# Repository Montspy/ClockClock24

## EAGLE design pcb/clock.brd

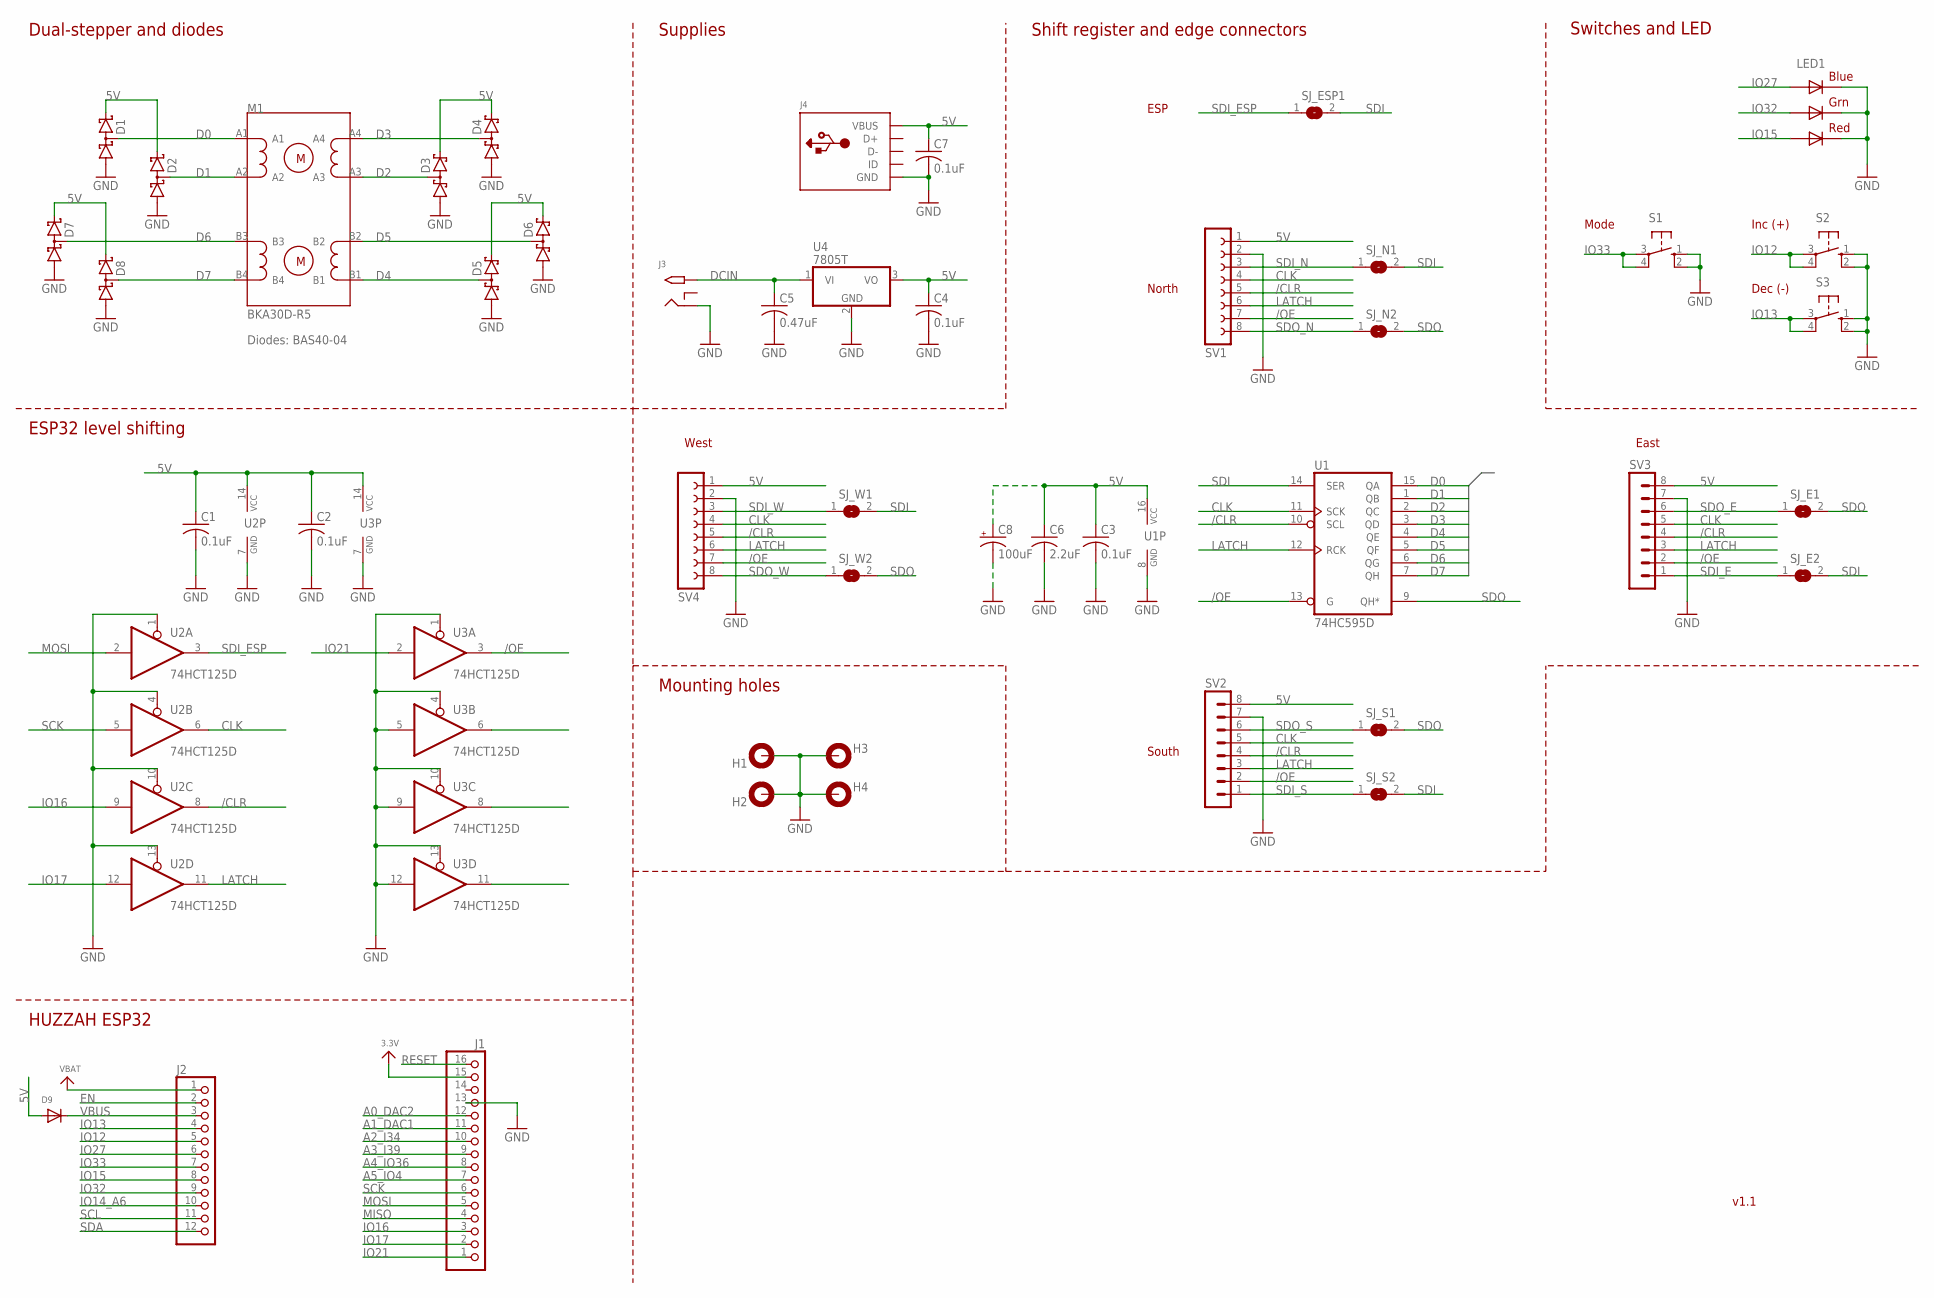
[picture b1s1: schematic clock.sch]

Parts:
C1, C2, C3, C4, C7: 0.1uF; C0805K
C5: 0.47uF; C0805K
C6: 2.2uF; C0805K
C8: 100uF; E3,5-8
D1, D2, D3, D4, D5, D6, D7, D8: BAS40-04; SOT23
D9: DIODEDO-1N4148; DO-1N4148
H1, H2, H3, H4: MOUNT-PAD-ROUND3.2; 3,2-PAD
J1: HEADER-1X16_MIN; 1X16_ROUND_MIN
J2: HEADER-1X12_MIN; 1X12_ROUND_MIN
J3: 2.1MMJACKTHM; PJ-102A
J4: USBMINIB; USB-MINIB
LED1: RGBLED5050
M1: BKA30D-R5
S1, S2, S3: 10-XX; B3F-10XX
SJ_E1, SJ_E2: SJ
SJ_ESP1: SJ
SJ_N1, SJ_N2: SJ
SJ_S1, SJ_S2: SJ
SJ_W1, SJ_W2: SJ
SV1, SV4: FE08W
SV2, SV3: MA08-1W
U1: 74HC595D; SO16
U2, U3: 74HCT125D; SO14
U4: 7805T; TO220H

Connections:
3.3V: J1.15
5V: C1.1, C2.1, C3.1, C4.1, C6.1, C7.1, C8.+, D1.2 (C2), D2.2 (C2), D3.2 (C2), D4.2 (C2), D5.2 (C2), D6.2 (C2), D7.2 (C2), D8.2 (C2), D9.A, J4.VBUS, SV1.1, SV2.8, SV3.8, SV4.1, U1.16 (VCC), U2.14 (VCC), U3.14 (VCC), U4.3 (VO)
/CLR: SV1.5, SV2.4, SV3.4, SV4.5, U1.10 (SCL), U2.8 (O)
/OE: SV1.7, SV2.2, SV3.2, SV4.7, U1.13 (G), U3.3 (O)
A0_DAC2: J1.12
A1_DAC1: J1.11
A2_I34: J1.10
A3_I39: J1.9
A4_IO36: J1.8
A5_IO4: J1.7
CLK: SV1.4, SV2.5, SV3.5, SV4.4, U1.11 (SCK), U2.6 (O)
D0: D1.3 (C1A2), M1.A1, U1.15 (QA)
D1: D2.3 (C1A2), M1.A2, U1.1 (QB)
D2: D3.3 (C1A2), M1.A3, U1.2 (QC)
D3: D4.3 (C1A2), M1.A4, U1.3 (QD)
D4: D5.3 (C1A2), M1.B1, U1.4 (QE)
D5: D6.3 (C1A2), M1.B2, U1.5 (QF)
D6: D7.3 (C1A2), M1.B3, U1.6 (QG)
D7: D8.3 (C1A2), M1.B4, U1.7 (QH)
DCIN: C5.1, J3.TIP, U4.1 (VI)
EN: J2.2
GND: C1.2, C2.2, C3.2, C4.2, C5.2, C6.2, C7.2, C8.-, D1.1 (A1), D2.1 (A1), D3.1 (A1), D4.1 (A1), D5.1 (A1), D6.1 (A1), D7.1 (A1), D8.1 (A1), H1.B3,2, H2.B3,2, H3.B3,2, H4.B3,2, J1.13, J3.RING, J4.GND, LED1.4 (BLUE_C), LED1.5 (RED_C), LED1.6 (GREEN_C), S1.1 (S), S1.2 (S1), S2.1 (S), S2.2 (S1), S3.1 (S), S3.2 (S1), SV1.2, SV2.7, SV3.7, SV4.2, U1.8 (GND), U2.1 (OE), U2.4 (OE), U2.7 (GND), U2.10 (OE), U2.13 (OE), U3.1 (OE), U3.4 (OE), U3.5 (I), U3.7 (GND), U3.9 (I), U3.10 (OE), U3.12 (I), U3.13 (OE), U4.2 (GND)
IO12: J2.5, S2.3, S2.4 (P1)
IO13: J2.4, S3.3, S3.4 (P1)
IO14_A6: J2.10
IO15: J2.8, LED1.2 (RED_A)
IO16: J1.3, U2.9 (I)
IO17: J1.2, U2.12 (I)
IO21: J1.1, U3.2 (I)
IO27: J2.6, LED1.3 (BLUE_A)
IO32: J2.9, LED1.1 (GREEN_A)
IO33: J2.7, S1.3, S1.4 (P1)
LATCH: SV1.6, SV2.3, SV3.3, SV4.6, U1.12 (RCK), U2.11 (O)
MISO: J1.4
MOSI: J1.5, U2.2 (I)
RESET: J1.16
SCK: J1.6, U2.5 (I)
SCL: J2.11
SDA: J2.12
SDI: SJ_E2.2, SJ_ESP1.2, SJ_N1.2, SJ_S2.2, SJ_W1.2, U1.14 (SER)
SDI_E: SJ_E2.1, SV3.1
SDI_ESP: SJ_ESP1.1, U2.3 (O)
SDI_N: SJ_N1.1, SV1.3
SDI_S: SJ_S2.1, SV2.1
SDI_W: SJ_W1.1, SV4.3
SDO: SJ_E1.2, SJ_N2.2, SJ_S1.2, SJ_W2.2, U1.9 (QH*)
SDO_E: SJ_E1.1, SV3.6
SDO_N: SJ_N2.1, SV1.8
SDO_S: SJ_S1.1, SV2.6
SDO_W: SJ_W2.1, SV4.8
VBAT: J2.1
VBUS: D9.C, J2.3

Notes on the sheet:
HUZZAH ESP32
ESP32 level shifting
Shift register and edge connectors
North
South
East
West
ESP
Diodes: BAS40-04
Dual-stepper and diodes
Switches and LED
Mode
Inc (+)
Dec (-)
Supplies
Mounting holes
v1.1

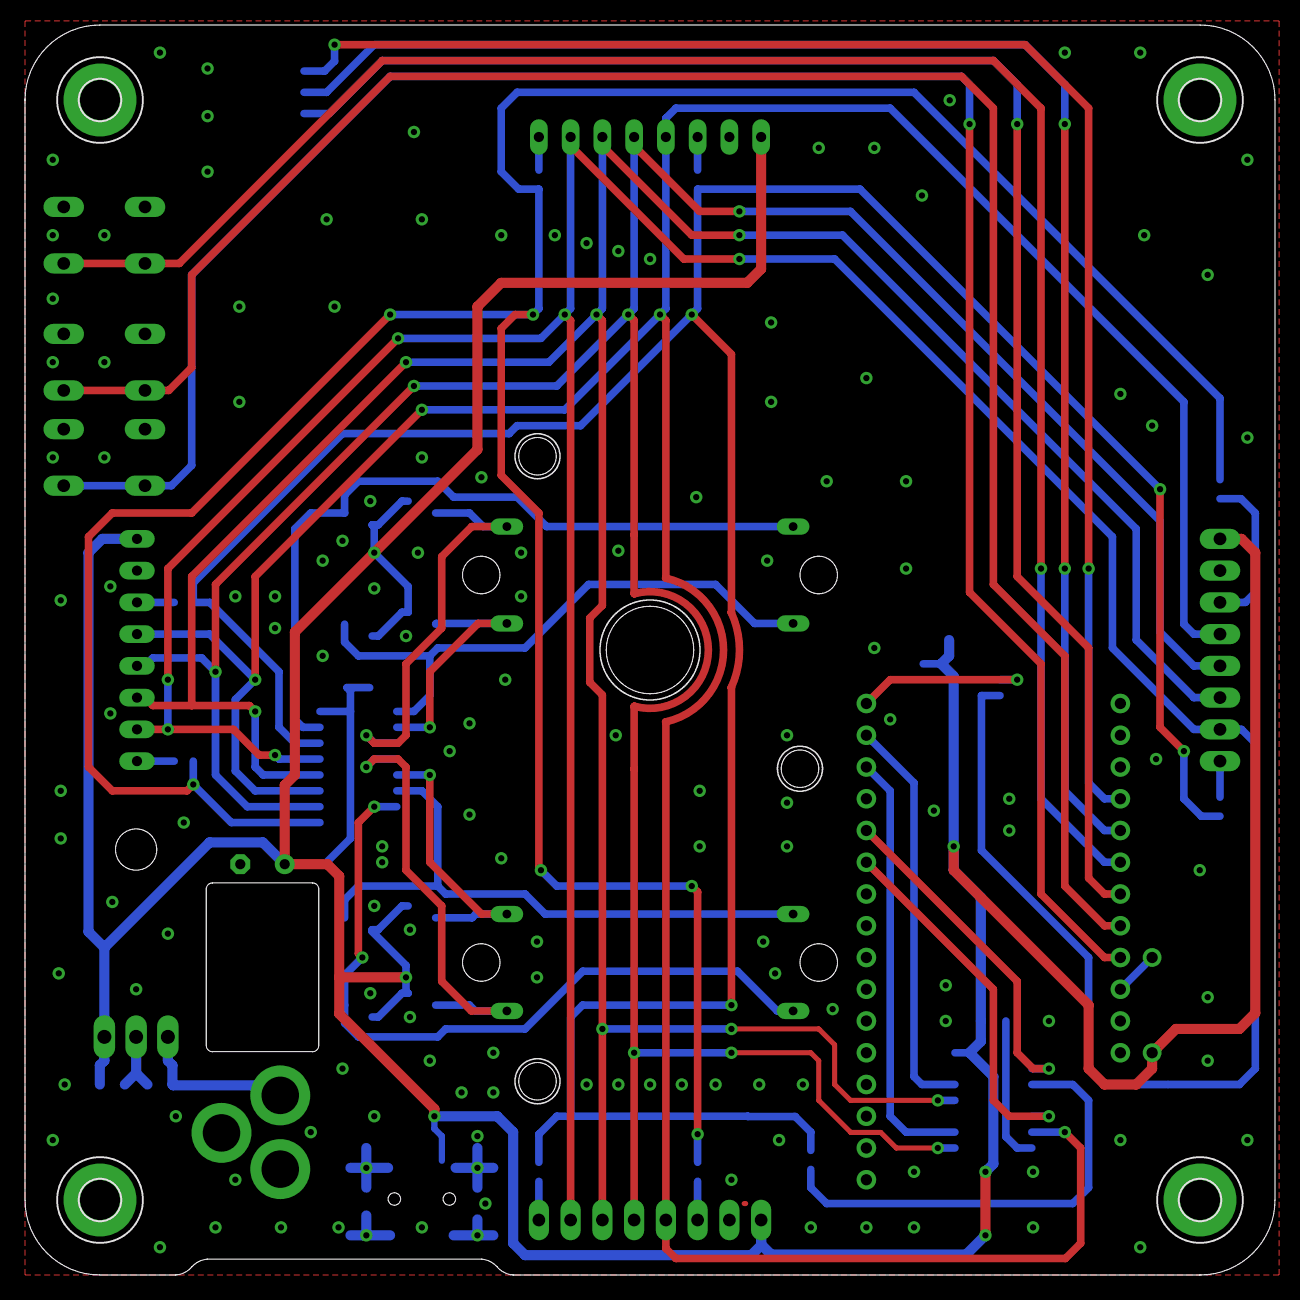
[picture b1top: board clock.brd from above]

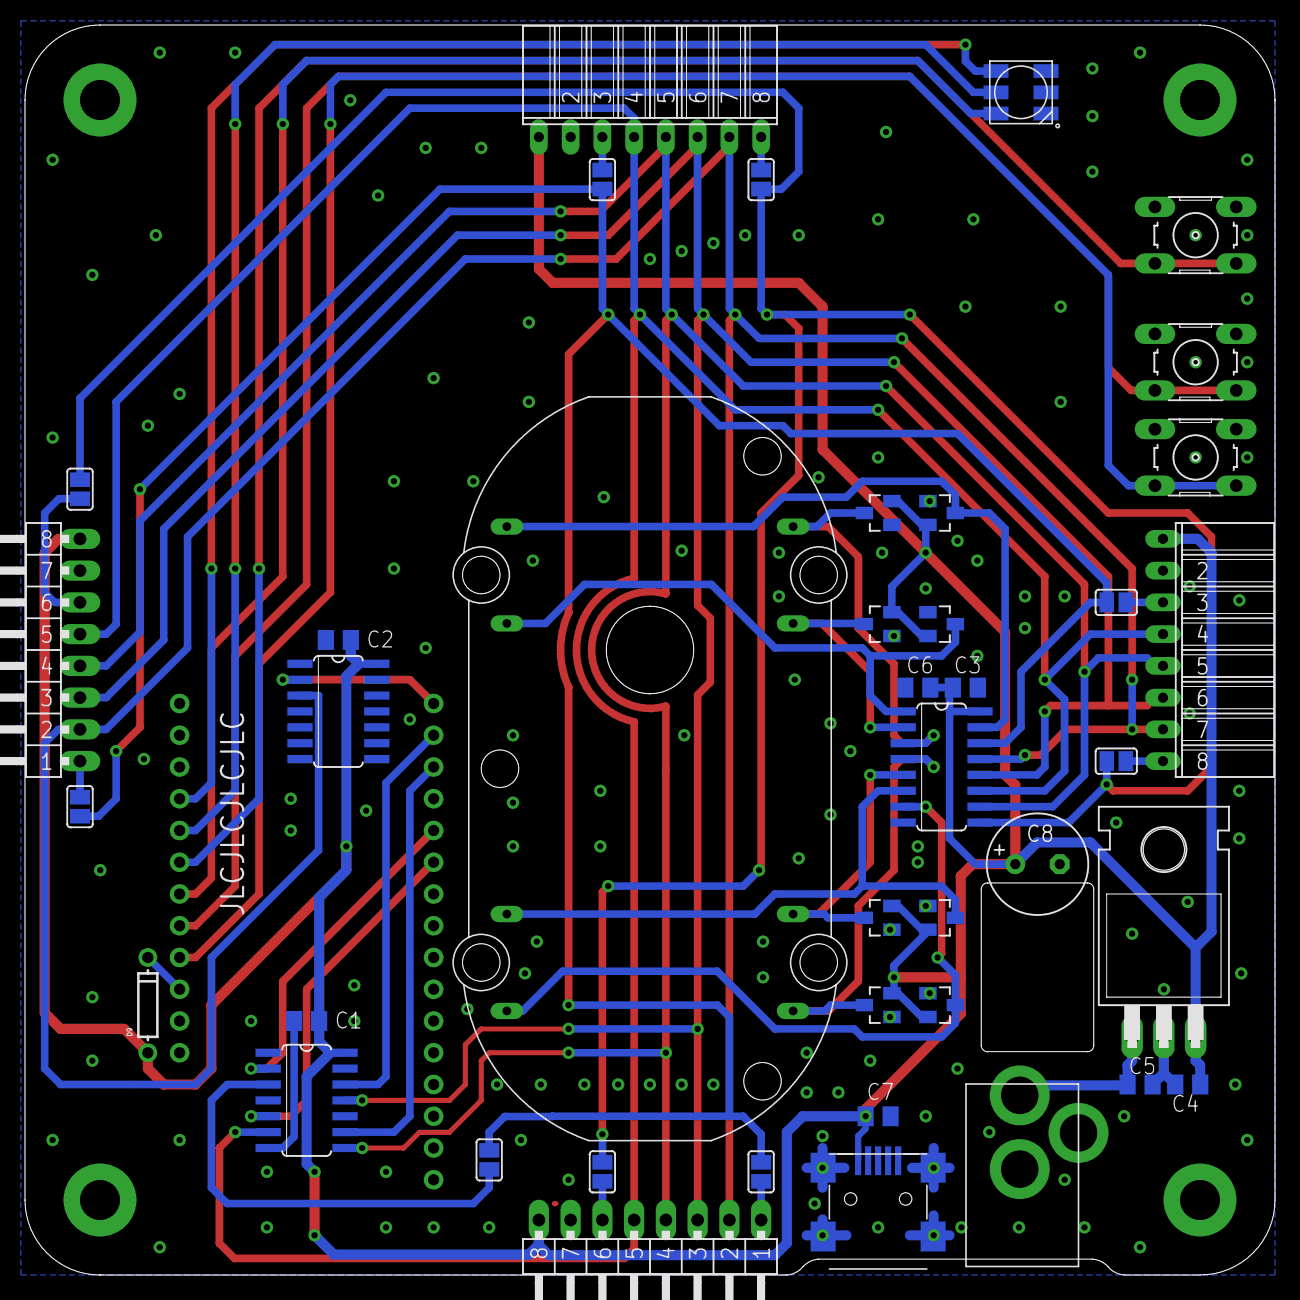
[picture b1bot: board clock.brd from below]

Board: 2 copper layers, 100.0 x 100.0 mm, 47 parts (43 on the bottom side), 38 nets.

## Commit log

2021-08-17 WIP codebase for v1.0 board
2021-08-17 README
2021-08-17 Added v1.0 pcb files for reference

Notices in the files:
parts and their libraries:
microbuilder: This work is placed in the public domain, and may be freely used for commercial and non-commercial work with the following conditions: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
